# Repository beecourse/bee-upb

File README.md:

bee-upb
=======

This [bee](https://github.com/beecourse) provides a **u**niversal **p**rototype **b**oard.

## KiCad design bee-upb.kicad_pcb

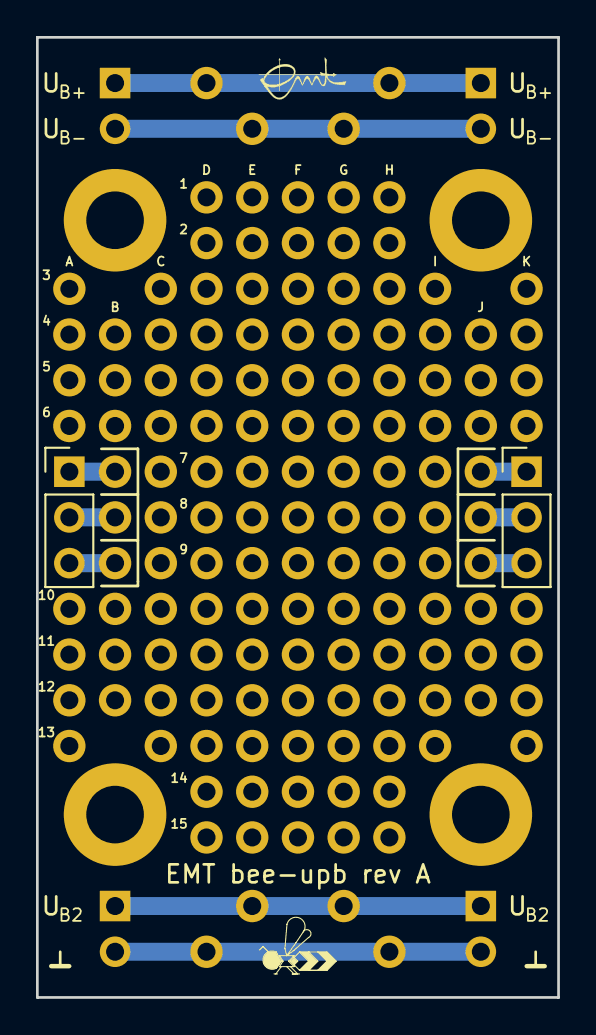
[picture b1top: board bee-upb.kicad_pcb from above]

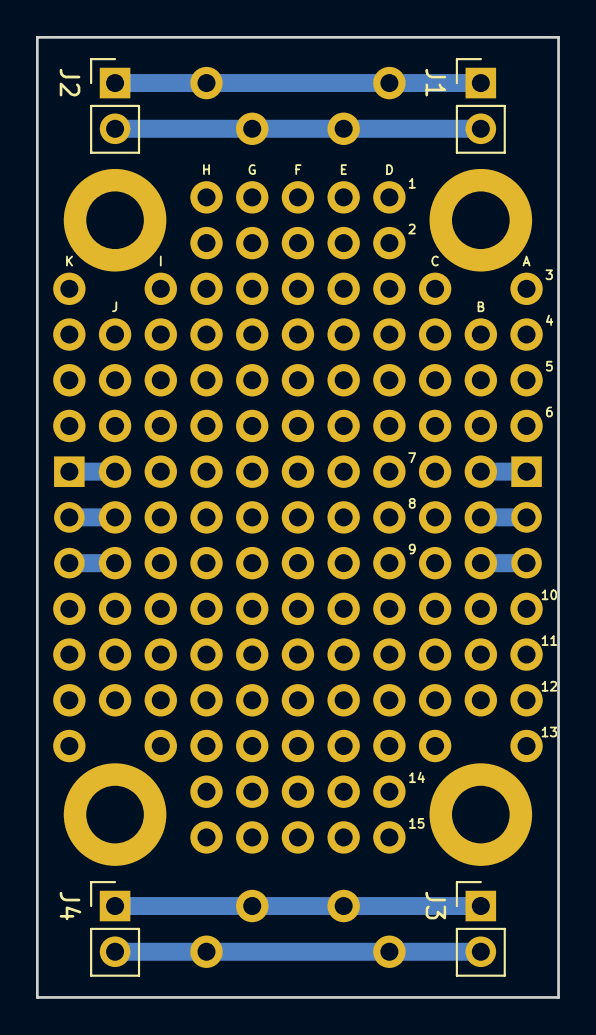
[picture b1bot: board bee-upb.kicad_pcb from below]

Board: 2 copper layers, 29.0 x 53.3 mm, 159 parts (4 on the bottom side), 10 nets.

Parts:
H1, H2: Silkscreen_Label; Text_U_B+_Silkscreen
H3, H4: Silkscreen_Label; Text_U_B-_Silkscreen
H5, H6: Silkscreen_Label; Text_U_B2_Silkscreen
H7, H8: Silkscreen_Label; Symbol_GND_Silkscreen
H9, H10, H11, H12: MountingHole_Pad; MountingHole_3.2mm_M3_ISO7380_Pad
H13: Silkscreen_Label; BEE-Logo_Silkscreen_small
H14: Silkscreen_Label; EMT-Logo_5.1x2.5mm_Silkscreen
J1, J2, J3, J4: Conn_01x02_Male; PinHeader_1x02_P2.54mm_Vertical
J5, J6: Conn_01x03; PinHeader_1x03_P2.54mm_Vertical
J7, J8, J9, J10, J11, J12, J13, J14, J15, J16, J17, J18, J19, J20, J21, J22, J23, J24, J25, J26, J27, J28, J29, J30, J31, J32, J33, J34, J35, J36, J37, J38, J39, J40, J41, J42, J43, J44, J45, J46, J47, J48, J49, J50, J51, J52, J53, J54, J55, J56, J57, J58, J59, J60, J61, J62, J63, J64, J65, J66, J67, J68, J69, J70, J71, J72, J73, J74, J75, J76, J77, J78, J79, J80, J81, J82, J83, J84, J85, J86, J87, J88, J89, J90, J91, J92, J93, J94, J95, J96, J97, J98, J99, J100, J101, J102, J103, J104, J105, J106, J107, J108, J109, J110, J111, J112, J113, J114, J115, J116, J117, J118, J119, J120, J121, J122, J123, J124, J125, J126, J127, J128, J129, J130, J131, J132, J133, J134, J135, J136, J137, J138, J139, J140, J141, J142, J143, J144, J145: Conn_01x01; TestPoint_THTPad_D1.8mm_Drill1.0mm

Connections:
+5V: J3.1, J4.1, J17.1, J18.1
+15V: J1.1, J2.1, J13.1, J14.1
-15V: J1.2, J2.2, J15.1, J16.1
GND: H9.1, H10.1, H11.1, H12.1, J3.2, J4.2, J19.1, J20.1
unnamed: J5.1, J9.1
unnamed: J5.2, J8.1
unnamed: J5.3, J7.1
unnamed: J6.3, J10.1
unnamed: J6.2, J11.1
unnamed: J6.1, J12.1

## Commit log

2020-12-10 Add .gitignore
2020-12-10 Add schematic and pcb
2020-12-10 Add license
2020-12-10 Add readme
2023-03-17 Add figure showing top view of PCB
